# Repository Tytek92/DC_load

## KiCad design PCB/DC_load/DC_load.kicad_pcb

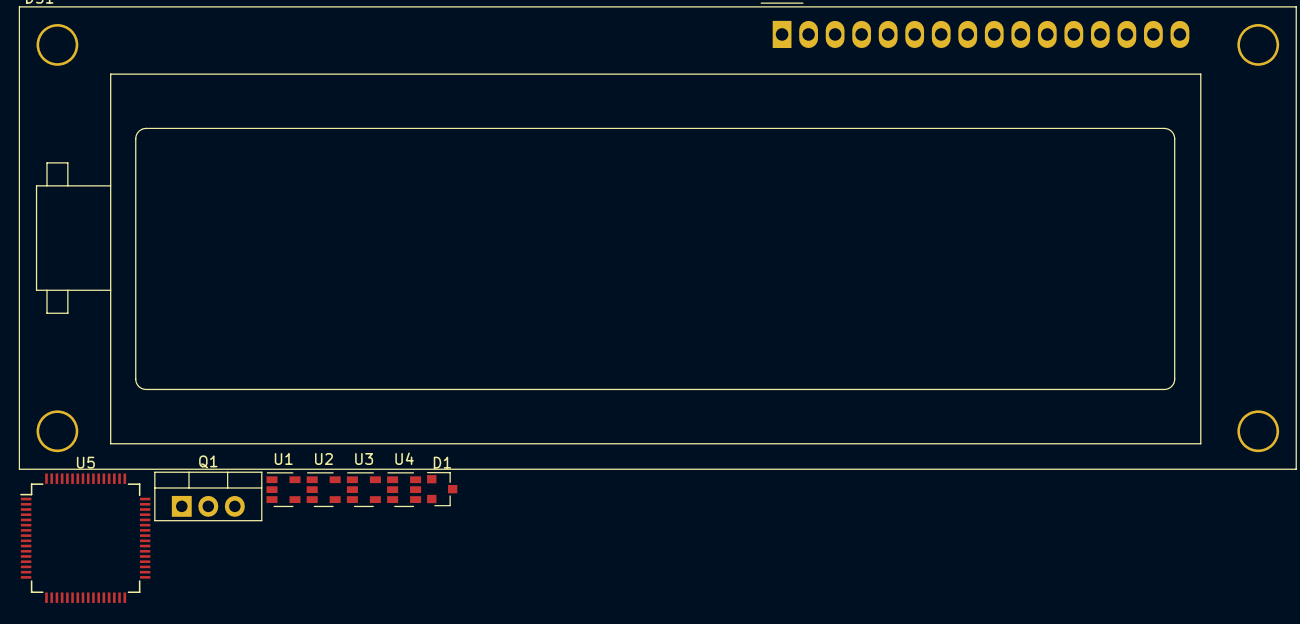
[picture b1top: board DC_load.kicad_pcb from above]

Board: 2 copper layers, 8 parts (0 on the bottom side), 6 nets, no tracks yet.

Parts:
D1: BAT54S; SOT-23
DS1: HY1602E
Q1: IRLB8721PBF; TO-220-3_Vertical
U1, U2, U3: LMV321IDBVR; SOT-23-5
U4: MCP3421A1T-ECH; SOT-23-6
U5: STM32F030R8Tx; LQFP-64_10x10mm_P0.5mm

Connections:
+3V3: D1.2, U1.5, U2.5, U3.5, U4.5
GND: D1.1, U1.2, U2.2, U3.2, U4.2, U4.6
NMOS_GATE: Q1.1, U1.3, U1.4
unnamed: D1.3, U3.1
unnamed: U2.4, U4.1
V_MEAS: U3.3, U3.4

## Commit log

2018-08-31 updated gitignore file for eclipse and kicad
2018-09-01 created kicad project and cubemx file
2018-09-02 prelimanary schematic
2018-09-02 schematic updated
